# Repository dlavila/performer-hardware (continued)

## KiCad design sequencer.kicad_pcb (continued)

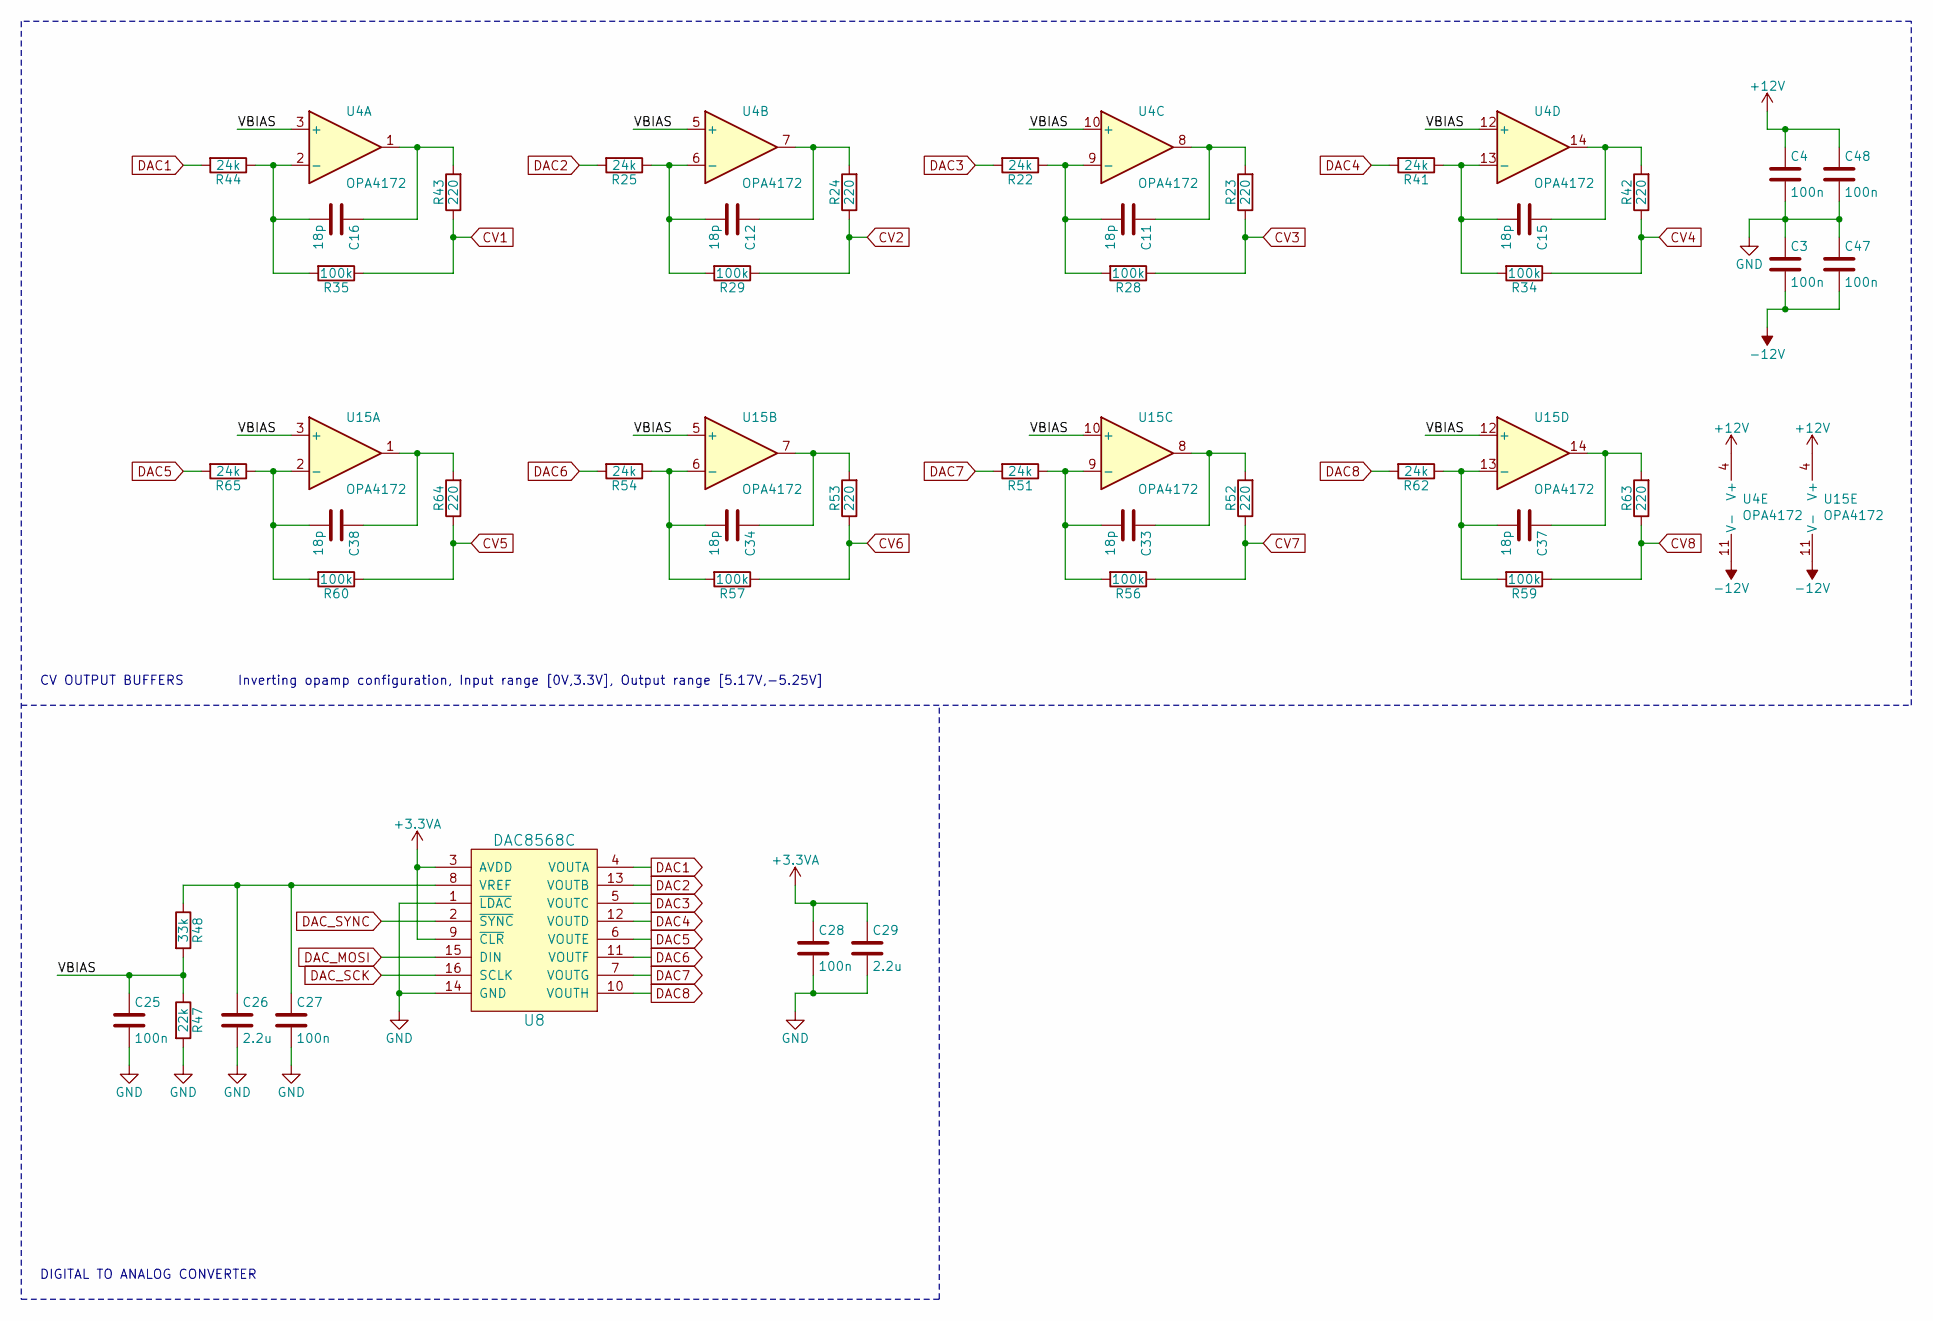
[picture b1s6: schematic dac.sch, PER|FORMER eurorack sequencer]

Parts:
C3, C4, C25, C27, C28, C47, C48: 100n; C_0603
C11, C12, C15, C16, C33, C34, C37, C38: 18p; C_0603
C26, C29: 2.2u; C_0603
R22, R25, R41, R44, R51, R54, R62, R65: 24k; R_0603
R23, R24, R42, R43, R52, R53, R63, R64: 220; R_0603
R28, R29, R34, R35, R56, R57, R59, R60: 100k; R_0603
R47: 22k; R_0603
R48: 33k; R_0603
U4, U15: OPA4172; SOIC-14_3.9x8.7mm_P1.27mm
U8: DAC8568C; TSSOP-16_4.4x5mm_P0.65mm

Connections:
+3.3VA: C28.1, C29.1, U8.3 (AVDD), U8.9 (~CLR); also elsewhere on the board
+12V: C4.1, C48.1, U4.4 (V+), U15.4 (V+); also elsewhere on the board
-12V: C3.2, C47.2, U4.11 (V-), U15.11 (V-); also elsewhere on the board
/DAC/VBIAS: C25.1, R47.1, R48.2, U4.3 (+), U4.5 (+), U4.10 (+), U4.12 (+), U15.3 (+), U15.5 (+), U15.10 (+), U15.12 (+)
CV1: R35.1, R43.1; also elsewhere on the board
CV2: R24.1, R29.1; also elsewhere on the board
CV3: R23.1, R28.1; also elsewhere on the board
CV4: R34.1, R42.1; also elsewhere on the board
CV5: R60.1, R64.1; also elsewhere on the board
CV6: R53.1, R57.1; also elsewhere on the board
CV7: R52.1, R56.1; also elsewhere on the board
CV8: R59.1, R63.1; also elsewhere on the board
DAC1: R44.2, U8.4 (VOUTA)
DAC2: R25.2, U8.13 (VOUTB)
DAC3: R22.2, U8.5 (VOUTC)
DAC4: R41.2, U8.12 (VOUTD)
DAC5: R65.2, U8.6 (VOUTE)
DAC6: R54.2, U8.11 (VOUTF)
DAC7: R51.2, U8.7 (VOUTG)
DAC8: R62.2, U8.10 (VOUTH)
DAC_MOSI: U8.15 (DIN); also elsewhere on the board
DAC_SCK: U8.16 (SCLK); also elsewhere on the board
DAC_SYNC: U8.2 (~SYNC); also elsewhere on the board
unnamed: C11.1, R23.2, U4.8
unnamed: C11.2, R22.1, R28.2, U4.9 (-)
unnamed: C12.1, R24.2, U4.7
unnamed: C12.2, R25.1, R29.2, U4.6 (-)
unnamed: C15.1, R42.2, U4.14
unnamed: C15.2, R34.2, R41.1, U4.13 (-)
unnamed: C16.1, R43.2, U4.1
unnamed: C16.2, R35.2, R44.1, U4.2 (-)
unnamed: C26.1, C27.1, R48.1, U8.8 (VREF)
unnamed: C33.1, R52.2, U15.8
unnamed: C33.2, R51.1, R56.2, U15.9 (-)
unnamed: C34.1, R53.2, U15.7
unnamed: C34.2, R54.1, R57.2, U15.6 (-)
unnamed: C37.1, R63.2, U15.14
unnamed: C37.2, R59.2, R62.1, U15.13 (-)
unnamed: C38.1, R64.2, U15.1
unnamed: C38.2, R60.2, R65.1, U15.2 (-)

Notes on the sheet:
CV OUTPUT BUFFERS
DIGITAL TO ANALOG CONVERTER
Inverting opamp configuration, Input range [0V,3.3V], Output range [5.17V,-5.25V]

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
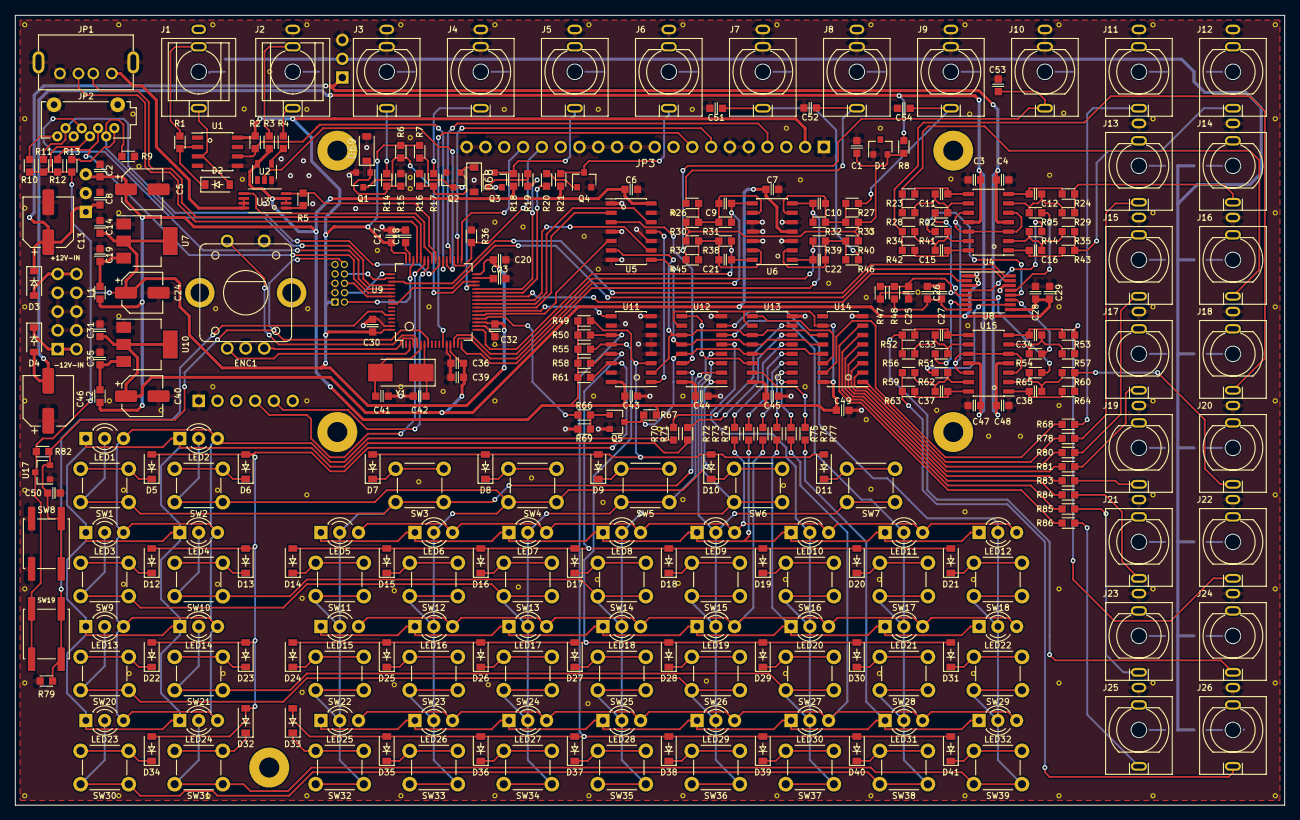
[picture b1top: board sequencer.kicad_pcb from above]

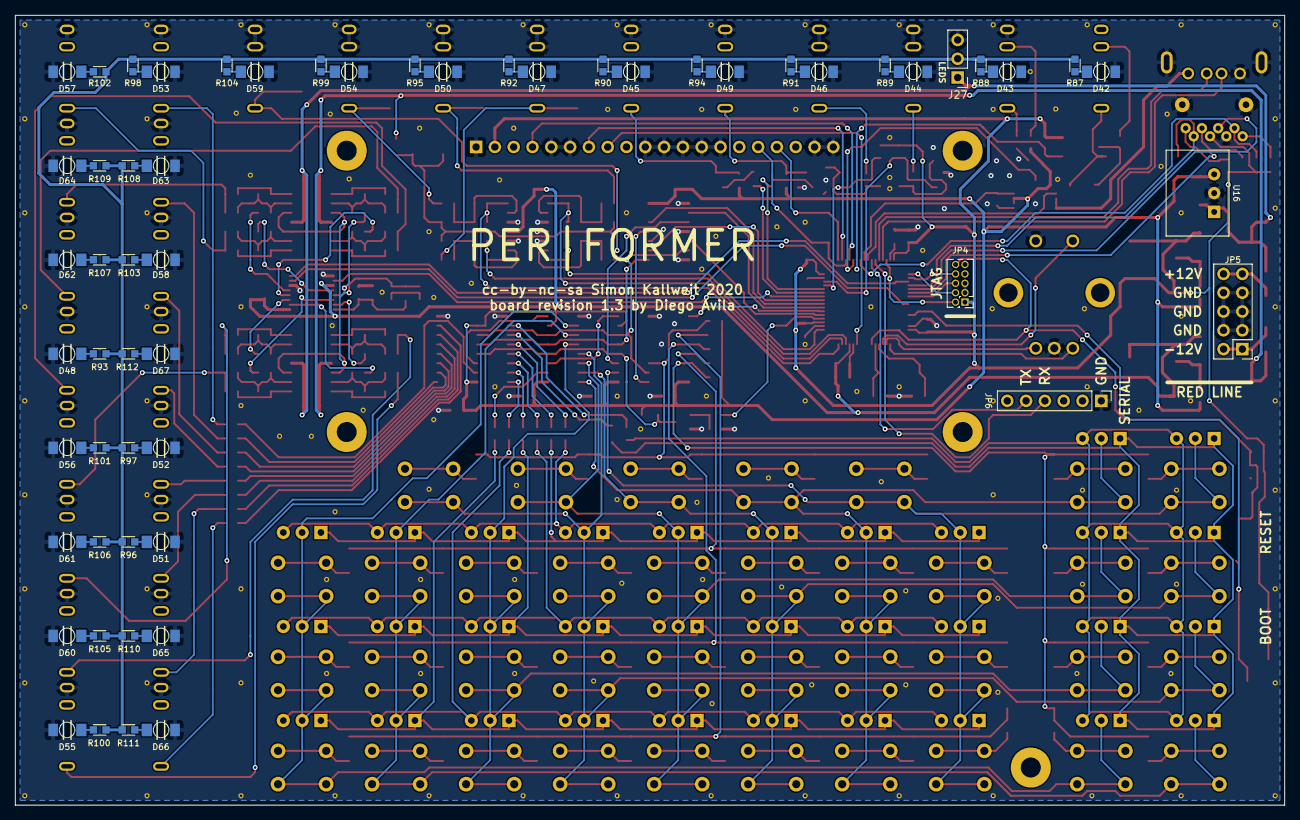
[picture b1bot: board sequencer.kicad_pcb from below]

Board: 2 copper layers, 171.4 x 106.7 mm, 365 parts (57 on the bottom side), 234 nets.

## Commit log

2019-04-08 fixed feedback capacitors
2019-04-08 replaced jacks with thonkiconns, updated pcb routing
2019-04-08 updated footprints
2019-04-08 moved usb connector up
2019-04-08 updated component values and revision
2020-06-25 add voltage supervisor, add leds to jacks, update footprints
2020-09-04 small changes
